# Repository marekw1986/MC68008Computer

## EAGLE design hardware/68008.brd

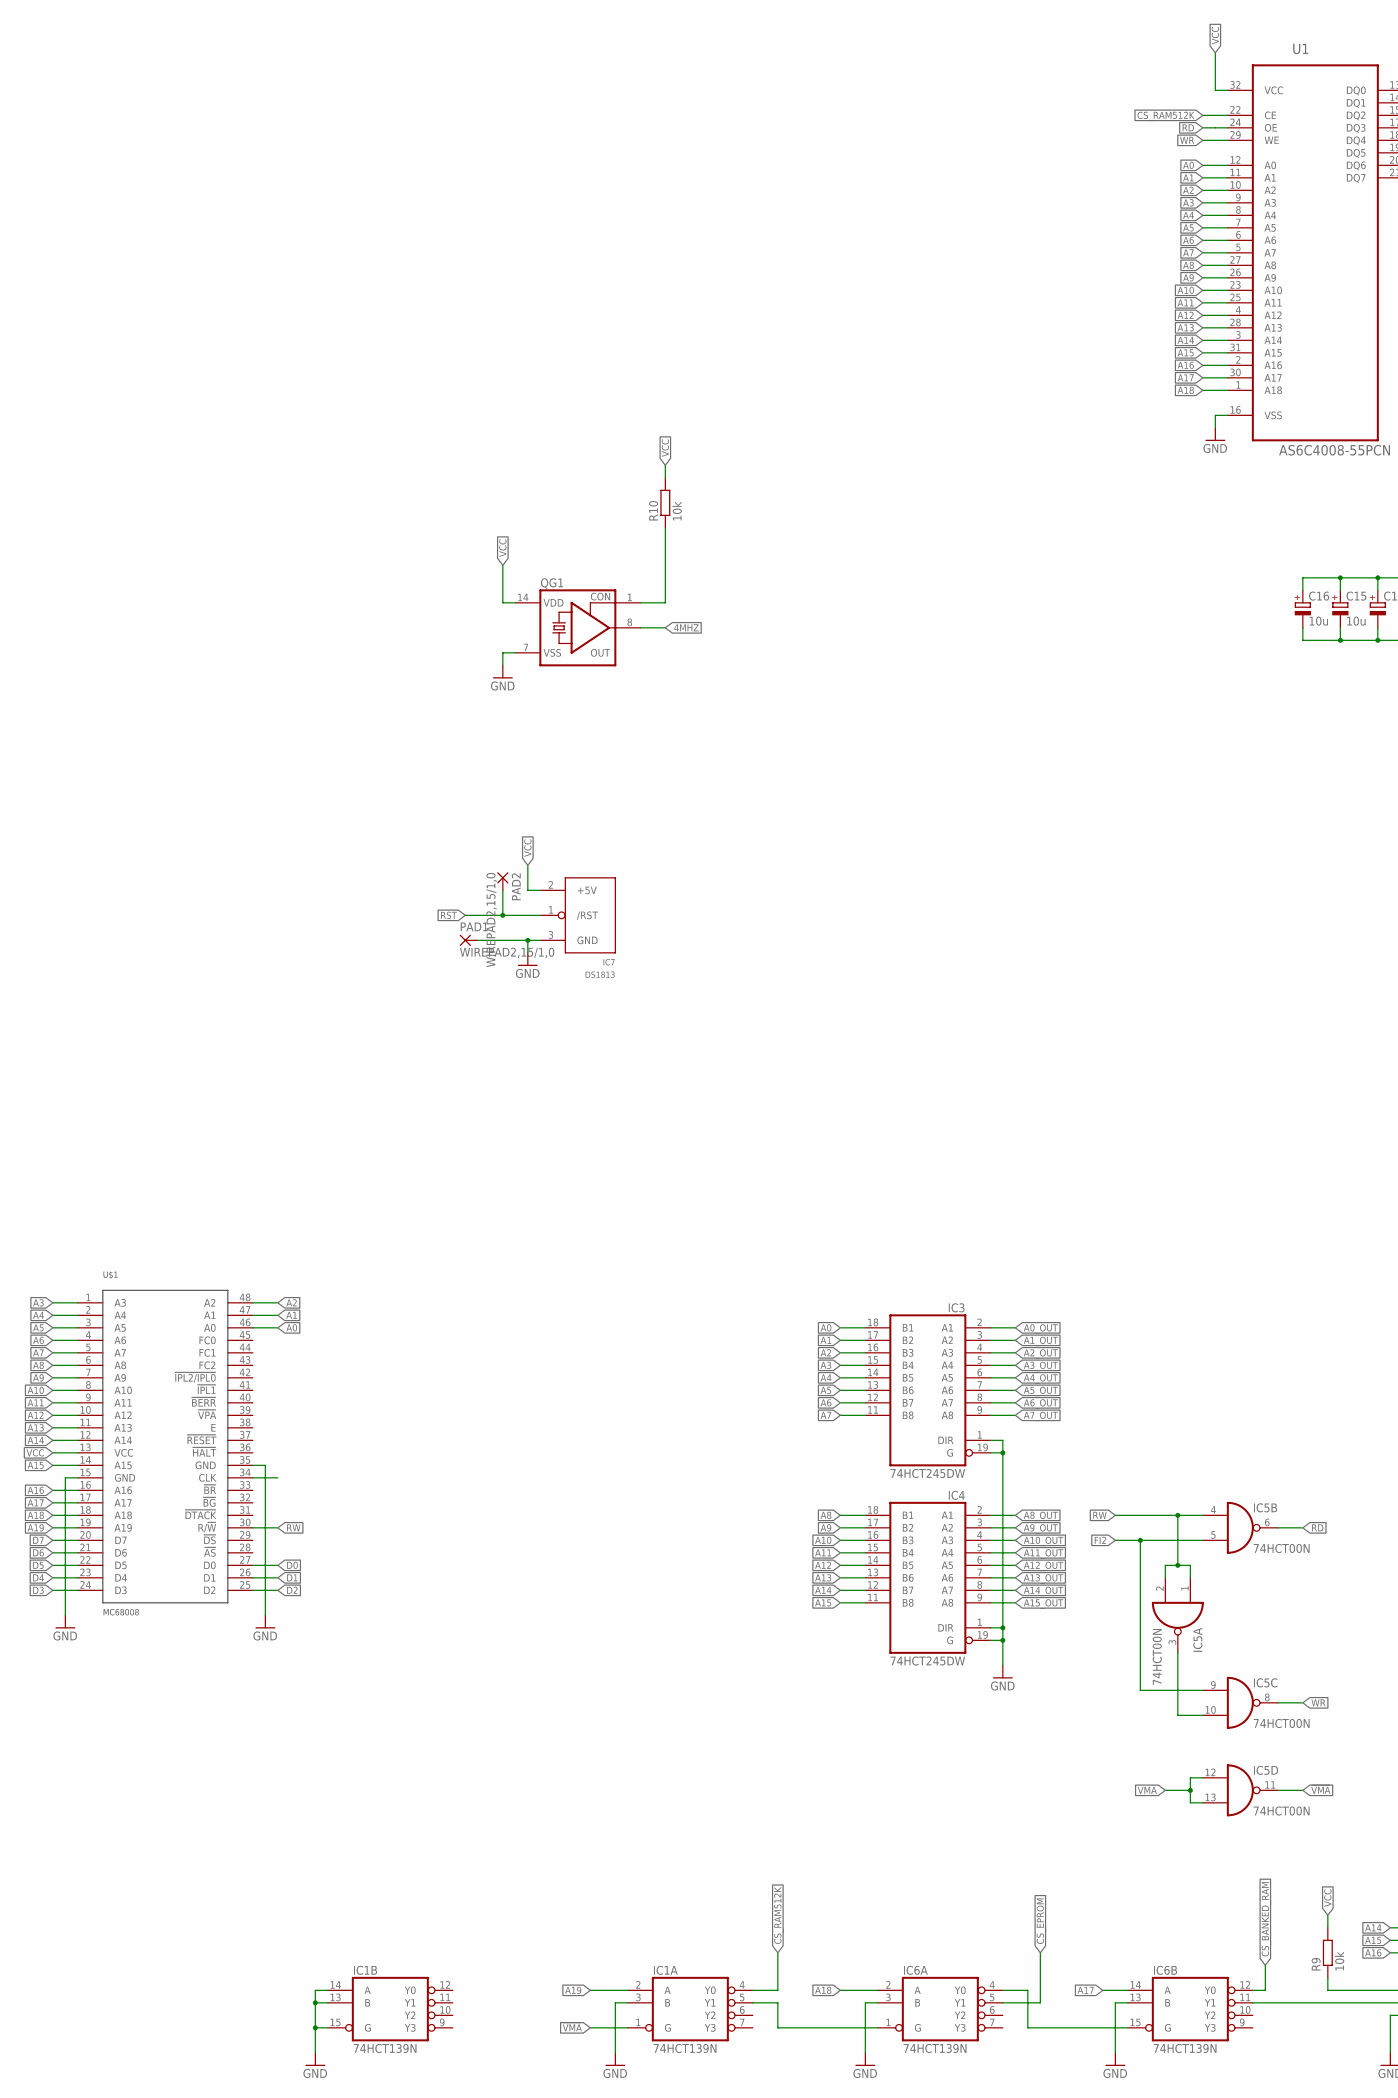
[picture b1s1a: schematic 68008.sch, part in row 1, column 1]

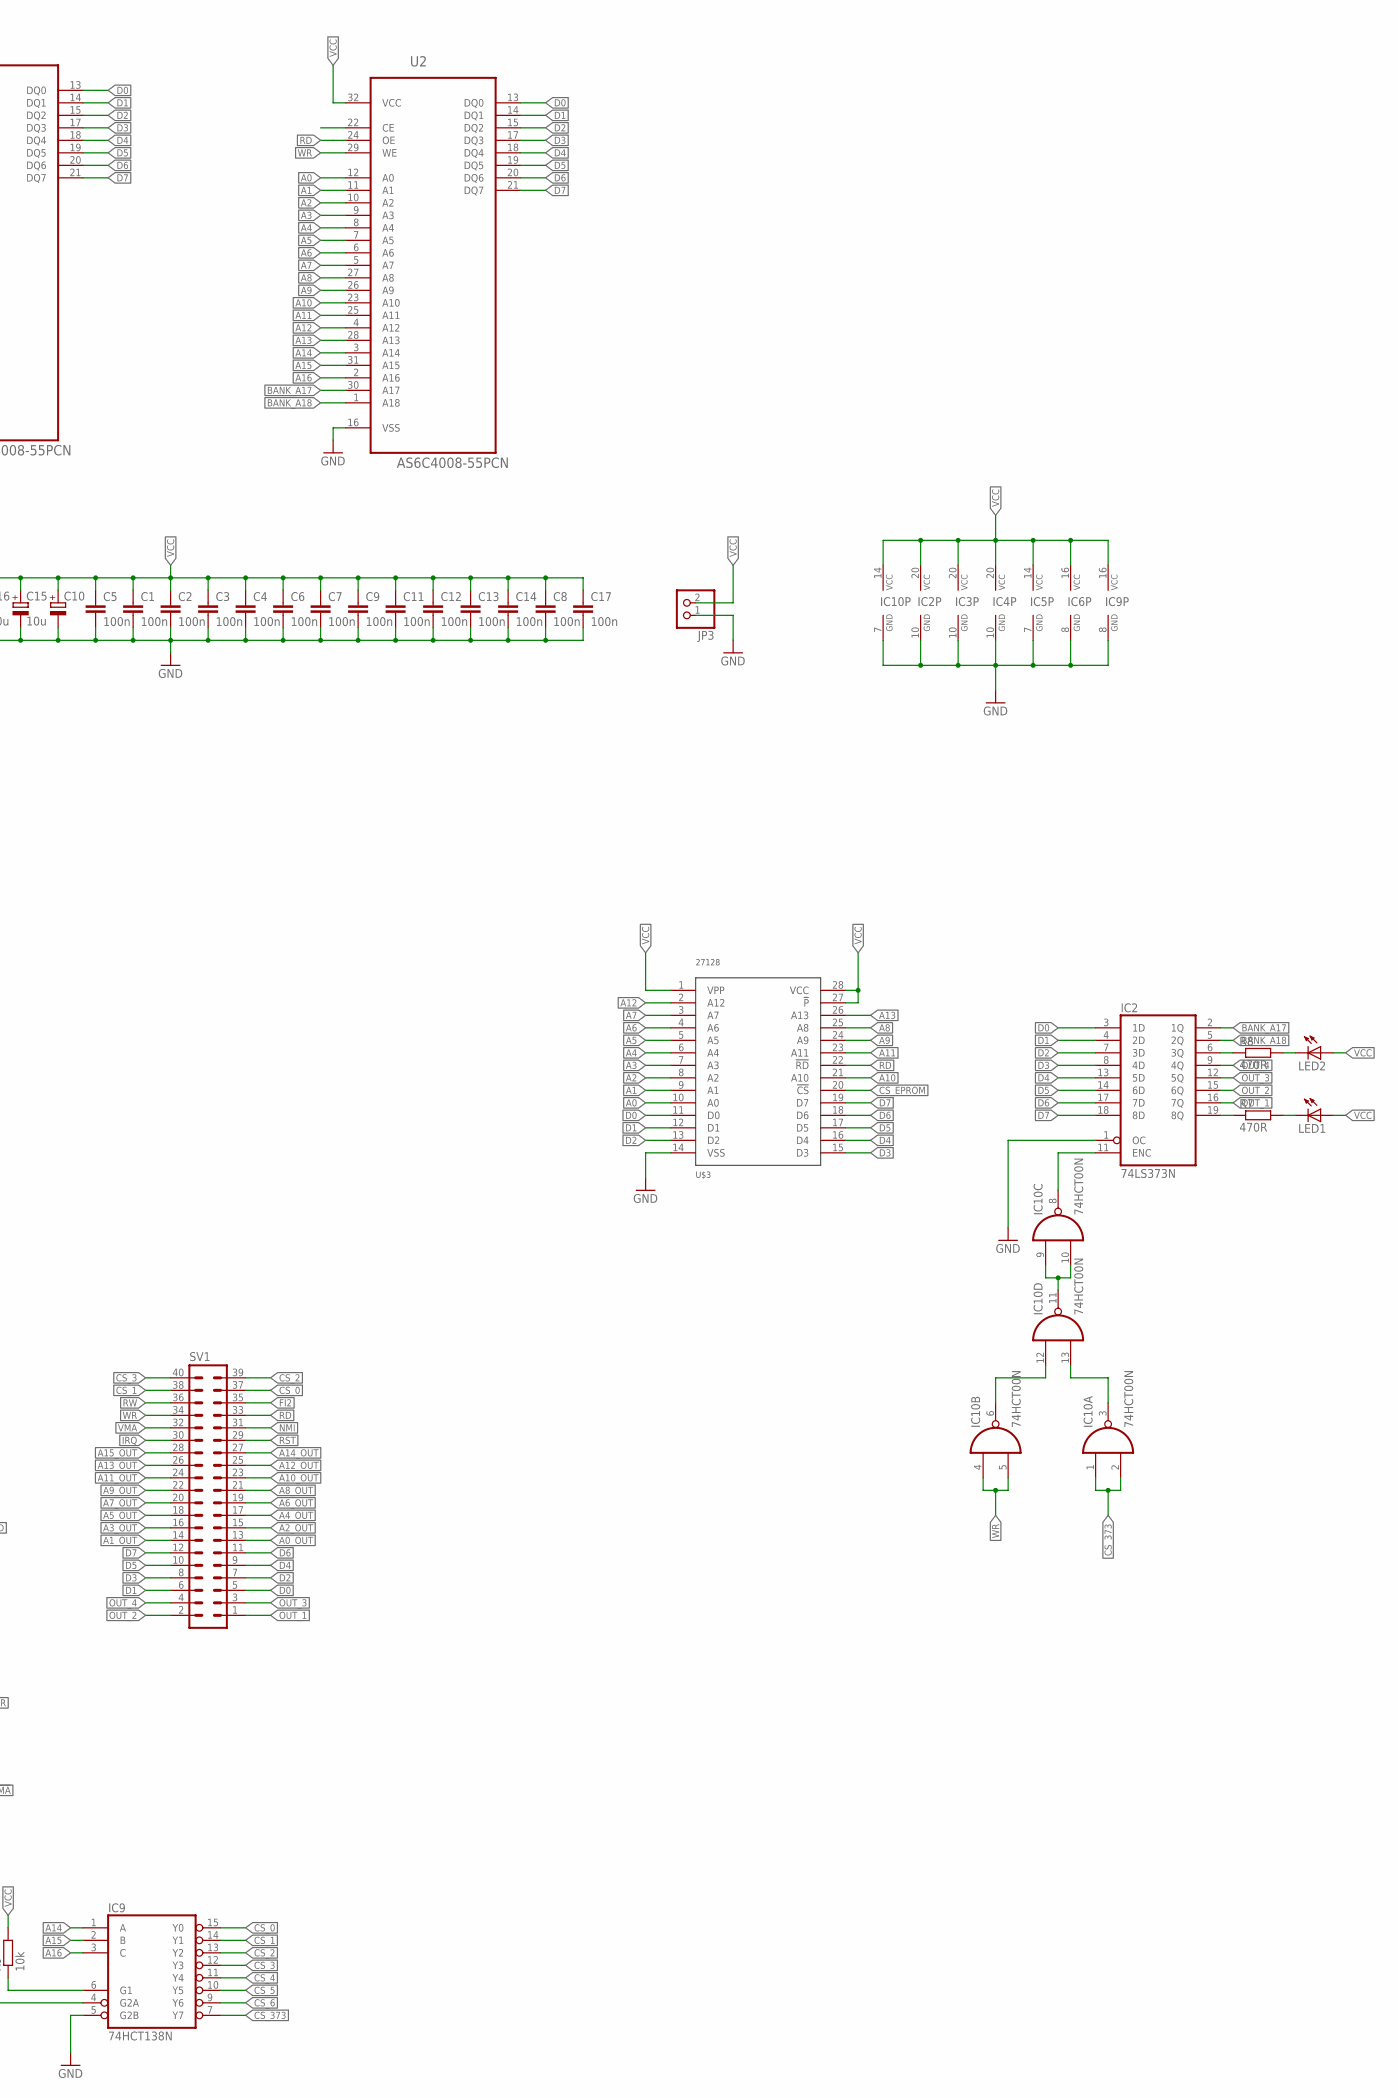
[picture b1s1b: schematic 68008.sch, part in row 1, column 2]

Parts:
C1, C2, C3, C4, C6, C8, C9: 100n; C1206
C5, C7, C14: 100n; C0603
C10: CPOL-EUE5-10.5; E5-10,5
C11, C12, C13, C17: 100n; C0805
C15, C16: 10u; SMC_B
IC1, IC6: 74HCT139N; DIL16
IC2: 74LS373N; DIL20
IC3, IC4: 74HCT245DW; SO20W
IC5, IC10: 74HCT00N; DIL14
IC7: DS1813; TO-92
IC9: 74HCT138N; DIL16
JP3: PINHD-1X2/90; 1X02/90
LED1, LED2: LED5MM
PAD1, PAD2: WIREPAD2,15/1,0; 2,15/1,0
QG1: CRYSTAL_RES-SG51; SG51
R7, R8: 470R; R1206
R9, R10: 10k; R1206
SV1: ML40L
U1, U2: AS6C4008-55PCN; DIP254P1524X393-32
U$1: MC68008; DIL48
U$3: 27128; DIL28

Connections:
4MHZ: QG1.8 (OUT)
!VMA: IC1.1 (G), IC5.11 (O)
A0: IC3.18 (B1), U1.12 (A0), U2.12 (A0), U$1.46 (A0), U$3.10 (A0)
A0_OUT: IC3.2 (A1), SV1.13
A1: IC3.17 (B2), U1.11 (A1), U2.11 (A1), U$1.47 (A1), U$3.9 (A1)
A1_OUT: IC3.3 (A2), SV1.14
A2: IC3.16 (B3), U1.10 (A2), U2.10 (A2), U$1.48 (A2), U$3.8 (A2)
A2_OUT: IC3.4 (A3), SV1.15
A3: IC3.15 (B4), U1.9 (A3), U2.9 (A3), U$1.1 (A3), U$3.7 (A3)
A3_OUT: IC3.5 (A4), SV1.16
A4: IC3.14 (B5), U1.8 (A4), U2.8 (A4), U$1.2 (A4), U$3.6 (A4)
A4_OUT: IC3.6 (A5), SV1.17
A5: IC3.13 (B6), U1.7 (A5), U2.7 (A5), U$1.3 (A5), U$3.5 (A5)
A5_OUT: IC3.7 (A6), SV1.18
A6: IC3.12 (B7), U1.6 (A6), U2.6 (A6), U$1.4 (A6), U$3.4 (A6)
A6_OUT: IC3.8 (A7), SV1.19
A7: IC3.11 (B8), U1.5 (A7), U2.5 (A7), U$1.5 (A7), U$3.3 (A7)
A7_OUT: IC3.9 (A8), SV1.20
A8: IC4.18 (B1), U1.27 (A8), U2.27 (A8), U$1.6 (A8), U$3.25 (A8)
A8_OUT: IC4.2 (A1), SV1.21
A9: IC4.17 (B2), U1.26 (A9), U2.26 (A9), U$1.7 (A9), U$3.24 (A9)
A9_OUT: IC4.3 (A2), SV1.22
A10: IC4.16 (B3), U1.23 (A10), U2.23 (A10), U$1.8 (A10), U$3.21 (A10)
A10_OUT: IC4.4 (A3), SV1.23
A11: IC4.15 (B4), U1.25 (A11), U2.25 (A11), U$1.9 (A11), U$3.23 (A11)
A11_OUT: IC4.5 (A4), SV1.24
A12: IC4.14 (B5), U1.4 (A12), U2.4 (A12), U$1.10 (A12), U$3.2 (A12)
A12_OUT: IC4.6 (A5), SV1.25
A13: IC4.13 (B6), U1.28 (A13), U2.28 (A13), U$1.11 (A13), U$3.26 (A13)
A13_OUT: IC4.7 (A6), SV1.26
A14: IC4.12 (B7), IC9.1 (A), U1.3 (A14), U2.3 (A14), U$1.12 (A14)
A14_OUT: IC4.8 (A7), SV1.27
A15: IC4.11 (B8), IC9.2 (B), U1.31 (A15), U2.31 (A15), U$1.14 (A15)
A15_OUT: IC4.9 (A8), SV1.28
A16: IC9.3 (C), U1.2 (A16), U2.2 (A16), U$1.16 (A16)
A17: IC6.14 (A), U1.30 (A17), U$1.17 (A17)
A18: IC6.2 (A), U1.1 (A18), U$1.18 (A18)
A19: IC1.2 (A), U$1.19 (A19)
BANK_A17: IC2.2 (1Q), U2.30 (A17)
BANK_A18: IC2.5 (2Q), U2.1 (A18)
CLK: U$1.34 (CLK)
CS_0: IC9.15 (Y0), SV1.37
CS_1: IC9.14 (Y1), SV1.38
CS_2: IC9.13 (Y2), SV1.39
CS_3: IC9.12 (Y3), SV1.40
CS_4: IC9.11 (Y4)
CS_5: IC9.10 (Y5)
CS_6: IC9.9 (Y6)
CS_373: IC9.7 (Y7), IC10.1 (I0), IC10.2 (I1)
CS_BANKED_RAM: IC6.12 (Y0), U2.22 (CE)
CS_EPROM: IC6.5 (Y1), U$3.20 (!CS)
CS_RAM512K: IC1.4 (Y0), U1.22 (CE)
D0: IC2.3 (1D), SV1.5, U1.13 (DQ0), U2.13 (DQ0), U$1.27 (D0), U$3.11 (D0)
D1: IC2.4 (2D), SV1.6, U1.14 (DQ1), U2.14 (DQ1), U$1.26 (D1), U$3.12 (D1)
D2: IC2.7 (3D), SV1.7, U1.15 (DQ2), U2.15 (DQ2), U$1.25 (D2), U$3.13 (D2)
D3: IC2.8 (4D), SV1.8, U1.17 (DQ3), U2.17 (DQ3), U$1.24 (D3), U$3.15 (D3)
D4: IC2.13 (5D), SV1.9, U1.18 (DQ4), U2.18 (DQ4), U$1.23 (D4), U$3.16 (D4)
D5: IC2.14 (6D), SV1.10, U1.19 (DQ5), U2.19 (DQ5), U$1.22 (D5), U$3.17 (D5)
D6: IC2.17 (7D), SV1.11, U1.20 (DQ6), U2.20 (DQ6), U$1.21 (D6), U$3.18 (D6)
D7: IC2.18 (8D), SV1.12, U1.21 (DQ7), U2.21 (DQ7), U$1.20 (D7), U$3.19 (D7)
FI2: IC5.5 (I1), IC5.9 (I0), SV1.35
GND: C1.2, C2.2, C3.2, C4.2, C5.2, C6.2, C7.2, C8.2, C9.2, C10.-, C11.2, C12.2, C13.2, C14.2, C15.-, C16.-, C17.2, IC1.3 (B), IC1.8 (GND), IC1.13 (B), IC1.14 (A), IC1.15 (G), IC2.1 (OC), IC2.10 (GND), IC3.1 (DIR), IC3.10 (GND), IC3.19 (G), IC4.1 (DIR), IC4.10 (GND), IC4.19 (G), IC5.7 (GND), IC6.3 (B), IC6.8 (GND), IC6.13 (B), IC7.3 (GND), IC9.5 (G2B), IC9.8 (GND), IC10.7 (GND), JP3.1, PAD1.1, QG1.7 (VSS), U1.16 (VSS), U2.16 (VSS), U$1.15 (GND), U$1.35 (GND), U$3.14 (VSS)
IRQ: SV1.30
unnamed: IC1.5 (Y1), IC6.1 (G)
unnamed: IC2.19 (8Q), R7.1
unnamed: LED1.K (C), R7.2
unnamed: QG1.1 (CON), R10.1
unnamed: IC2.11 (ENC), IC10.8 (O)
unnamed: IC10.9 (I0), IC10.10 (I1), IC10.11 (O)
unnamed: IC10.3 (O), IC10.13 (I1)
unnamed: IC10.6 (O), IC10.12 (I0)
unnamed: IC2.6 (3Q), R8.1
unnamed: LED2.K (C), R8.2
unnamed: IC5.3 (O), IC5.10 (I1)
unnamed: IC6.4 (Y0), IC6.15 (G)
unnamed: IC9.6 (G1), R9.1
unnamed: IC6.11 (Y1), IC9.4 (G2A)
NMI: SV1.31
OUT_1: IC2.16 (7Q), SV1.1
OUT_2: IC2.15 (6Q), SV1.2
OUT_3: IC2.12 (5Q), SV1.3
OUT_4: IC2.9 (4Q), SV1.4
RD: IC5.6 (O), SV1.33, U1.24 (OE), U2.24 (OE), U$3.22 (!RD)
RST: IC7.1 (/RST), PAD2.1, SV1.29
RW: IC5.1 (I0), IC5.2 (I1), IC5.4 (I0), SV1.36, U$1.30 (R/!W)
VCC: C1.1, C2.1, C3.1, C4.1, C5.1, C6.1, C7.1, C8.1, C9.1, C10.+, C11.1, C12.1, C13.1, C14.1, C15.+, C16.+, C17.1, IC1.16 (VCC), IC2.20 (VCC), IC3.20 (VCC), IC4.20 (VCC), IC5.14 (VCC), IC6.16 (VCC), IC7.2 (+5V), IC9.16 (VCC), IC10.14 (VCC), JP3.2, LED1.A, LED2.A, QG1.14 (VDD), R9.2, R10.2, U1.32 (VCC), U2.32 (VCC), U$1.13 (VCC), U$3.1 (VPP), U$3.27 (!P), U$3.28 (VCC)
VMA: IC5.12 (I0), IC5.13 (I1), SV1.32
WR: IC5.8 (O), IC10.4 (I0), IC10.5 (I1), SV1.34, U1.29 (WE), U2.29 (WE)

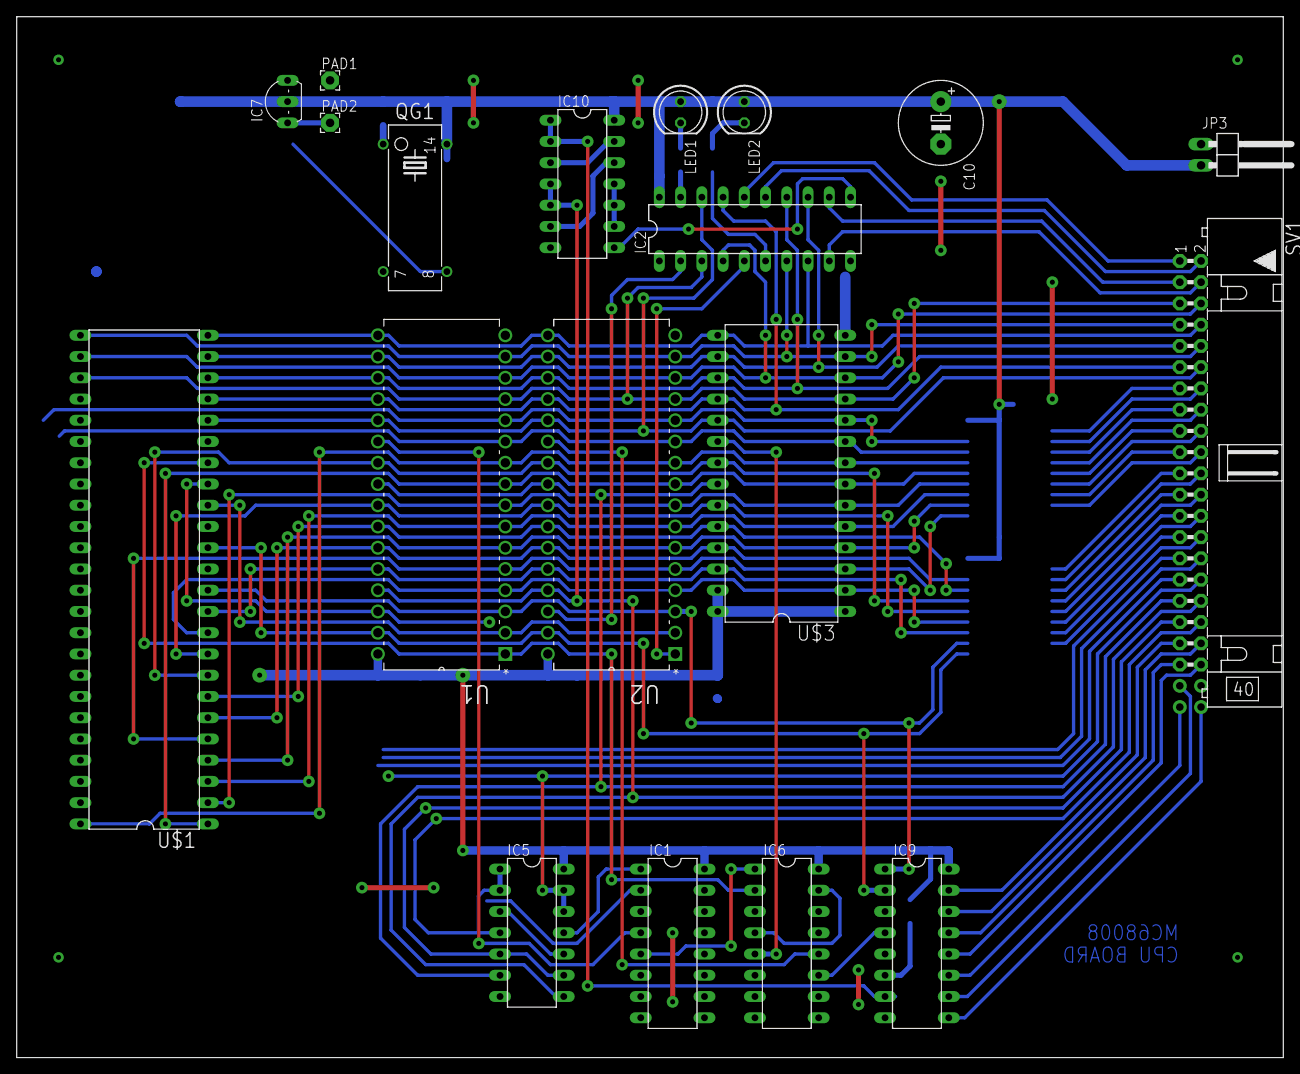
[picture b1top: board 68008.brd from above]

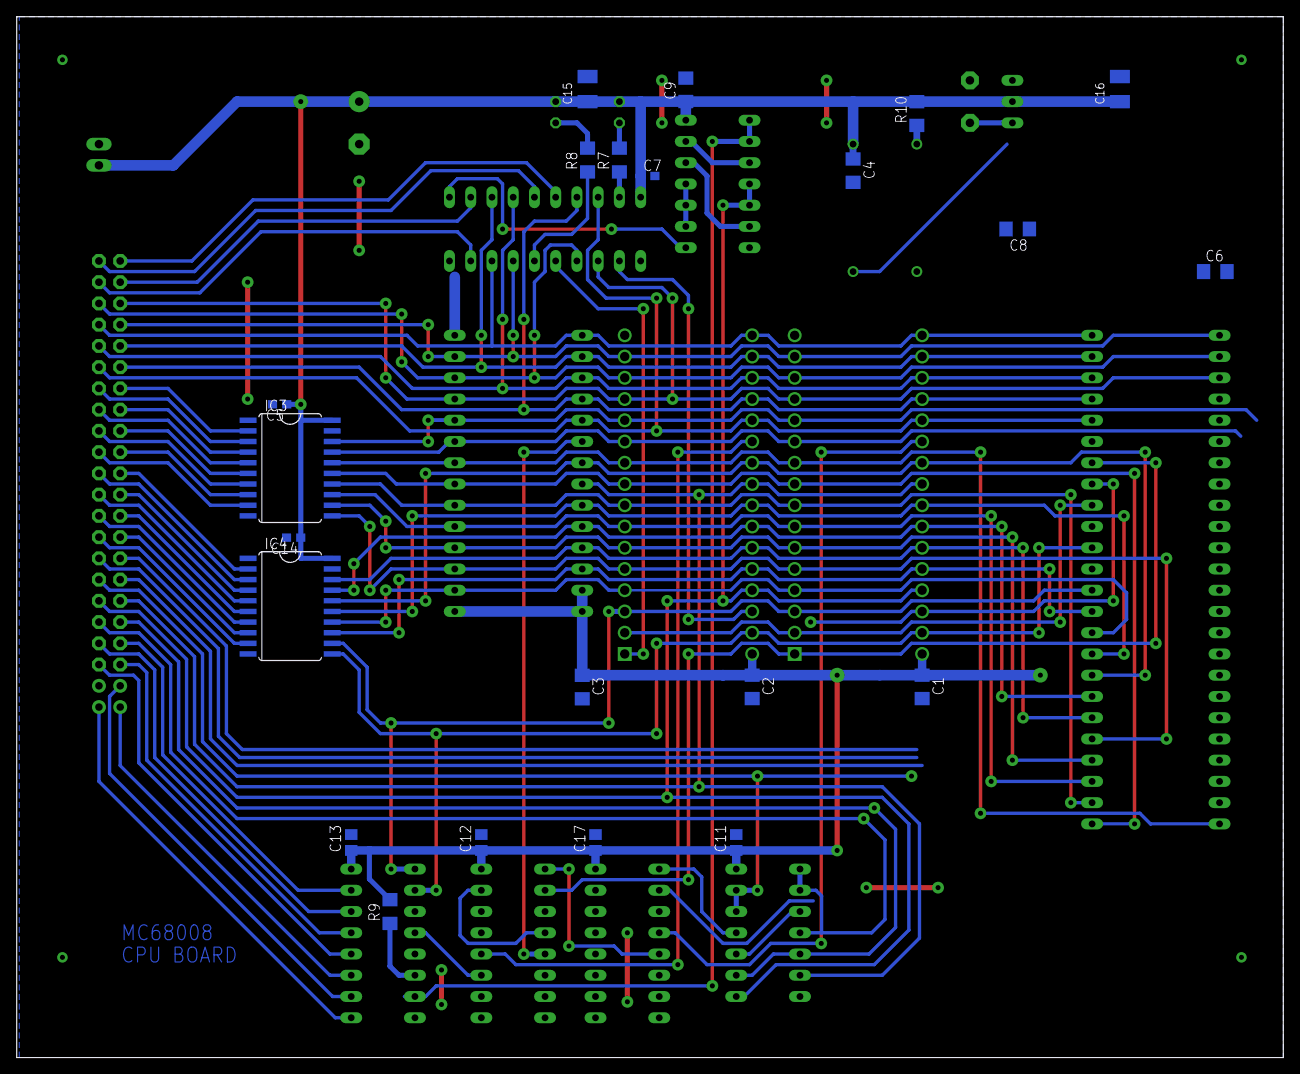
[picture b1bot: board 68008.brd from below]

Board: 2 copper layers, 151.4 x 124.5 mm, 41 parts (22 on the bottom side), 81 nets.

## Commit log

2024-06-26 PCB updated
